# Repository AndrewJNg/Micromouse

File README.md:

# Micromouse
Micromouse alagorithm for solving a maze with known size

## Current robot: 
1. Homemade micromouse (Arduino Micro) 
2. ESP32 micromouse

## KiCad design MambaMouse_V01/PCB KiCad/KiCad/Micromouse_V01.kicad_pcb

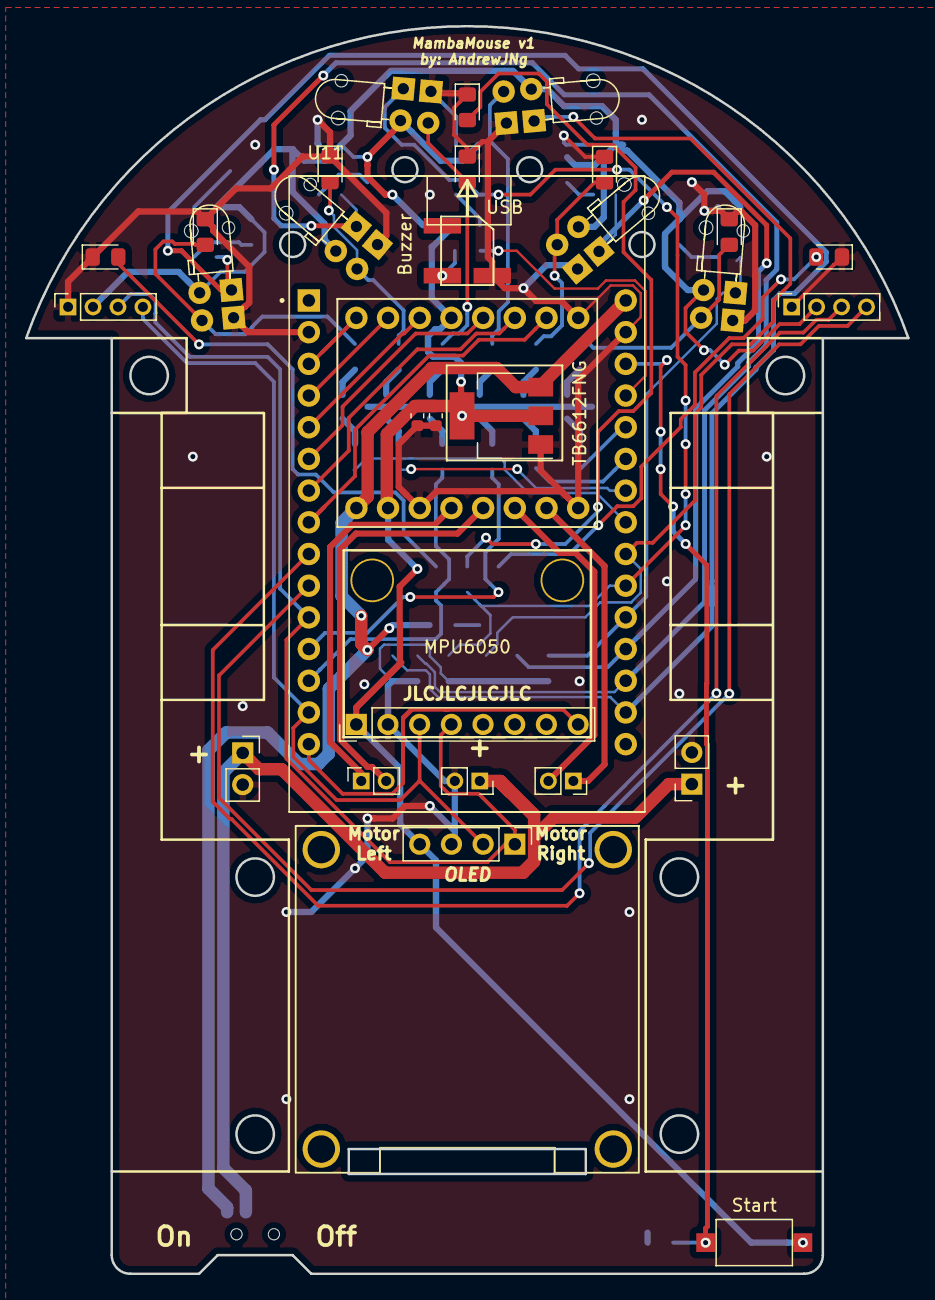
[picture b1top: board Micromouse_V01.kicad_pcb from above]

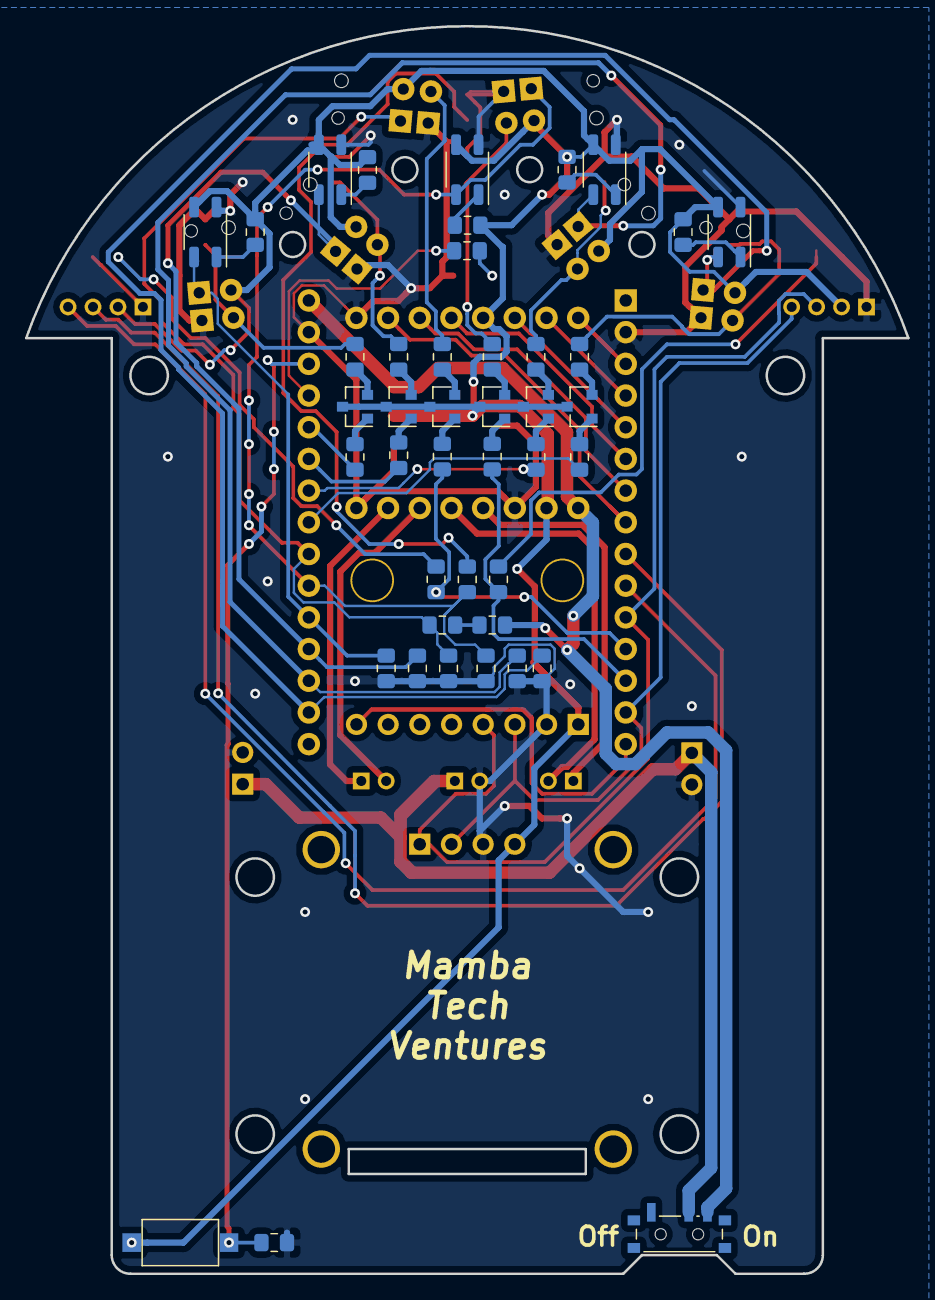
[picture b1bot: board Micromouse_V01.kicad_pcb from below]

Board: 2 copper layers, 70.7 x 100.0 mm, 73 parts (43 on the bottom side), 61 nets.

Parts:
BZ1: Buzzer; 4.2mm_5.5mm buzzer
C1, C2: 100nF; C_0603_1608Metric
D1, D2, D3, D4, D5, D6, D7, D8: LED; LED_0805_2012Metric_Pad1.15x1.40mm_HandSolder
J1, J7: Conn_01x02_Female; PinSocket_1x02_P2.54mm_Vertical
J2, J4, J8: Conn_01x02_Female; PinSocket_1x02_P2.00mm_Vertical
J3: OLED; OLED 128x32
J5: AS5600 Left; PinSocket_1x04_P2.00mm_Vertical
J6: AS5600 Right; PinSocket_1x04_P2.00mm_Vertical
Q1, Q2, Q3, Q4, Q5, Q6: Q_NPN_BEC; SOT-23
R1, R3, R5, R7, R9, R11, R15, R16, R17, R19, R26, R27, R28, R29, R30: 100; R_0805_2012Metric_Pad1.15x1.40mm_HandSolder
R2, R4, R6, R8, R10, R12, R13, R14, R18: 10K; R_0805_2012Metric_Pad1.15x1.40mm_HandSolder
R20, R21, R22, R23, R24, R25: 1k; R_0805_2012Metric_Pad1.15x1.40mm_HandSolder
S1, S2, S3, S4, S5, S6: 3mm_IR
S7, S8, S9, S10, S11: QRE1113; OnSemi_CASE100CY
SW1: SW_DPDT_x2; SW_SPDT_PCM12
SW2, SW3: Start; SW_SPST_CK_RS282G05A3
U1: AMS1117-3.3; SOT-223-3_TabPin2
U11: ESP32-WROOM; MODULE_ESP32_DEVKIT_V1
U12: TB6612FNG
U13: MPU-6050; MPU6050 module

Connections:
1: R15.1, R25.2, U11.35
2: U11.24, U12.22
3: R17.1, R20.2, U11.34
4: U11.26, U12.21
5: U11.29, U12.15
12: R19.1, U11.14
13: R18.2, SW2.2, SW3.2, U11.16
14: R24.2, U11.13
15: U11.23, U12.23
16: U11.27, U12.17
17: U11.28, U12.16
18_SDA2: J6.3, U11.30
19_SCL2: J6.4, U11.31
21_SDA1: J3.4, J5.3, U11.33, U13.24
22_SCL1: J3.3, J5.4, U11.36, U13.23
23: U11.37, U13.12
25: R21.2, U11.10
26: R22.2, U11.11
27: R23.2, U11.12
32: R10.1, R16.1, S5.3, S9.4, U11.8
33: R12.1, R14.2, S6.3, U11.9
34: R6.1, S3.3, S10.4, U11.6
35: R8.1, S4.3, S11.4, U11.7
36: R2.1, S1.3, S7.4, U11.4
39: R4.1, S2.3, S8.4, U11.5
+3V3: C1.1, C2.1, J3.1, J5.2, J6.2, Q1.3, Q2.3, Q3.3, Q4.3, Q5.3, Q6.3, R26.1, R27.1, R28.1, R29.1, R30.1, S1.4, S2.4, S3.4, S4.4, S5.4, S6.4, S7.3, S8.3, S9.3, S10.3, S11.3, SW2.1, SW3.1, U1.2, U12.19, U12.20, U13.13
+BATT: J1.1, J7.1, J8.1, SW1.2
GND: BZ1.2, C1.2, C2.2, D1.1, D2.1, D3.1, D4.1, D5.1, D6.1, D7.1, D8.1, J1.2, J3.2, J5.1, J6.1, J7.2, J8.2, R2.2, R4.2, R6.2, R8.2, R10.2, R12.2, R18.1, S1.1, S2.1, S3.1, S4.1, S5.1, S6.1, S7.2, S8.2, S9.2, S10.2, S11.2, U1.1, U11.15, U12.4, U12.9, U12.18, U13.18
unnamed: BZ1.1, R19.2
unnamed: D1.2, R15.2
unnamed: D2.2, R16.2
unnamed: D3.2, R17.2
unnamed: D4.2, R1.2, S1.2
unnamed: D5.2, R3.2, S2.2
unnamed: D6.2, R9.2, S5.2
unnamed: D7.2, R5.2, S3.2
unnamed: D8.2, R7.2, S4.2
unnamed: J2.1, U12.1
unnamed: J2.2, U12.5
unnamed: J4.1, U12.11
unnamed: J4.2, U12.7
unnamed: Q1.1, R21.1
unnamed: Q1.2, R1.1
unnamed: Q2.1, R22.1
unnamed: Q2.2, R3.1
unnamed: Q3.1, R23.1
unnamed: Q3.2, R5.1
unnamed: Q4.1, R24.1
unnamed: Q4.2, R7.1
unnamed: Q5.1, R25.1
unnamed: Q5.2, R9.1
unnamed: Q6.1, R20.1
unnamed: Q6.2, R11.1
unnamed: R11.2, S6.2
unnamed: R13.2, R14.1
unnamed: R26.2, S9.1
unnamed: R27.2, S7.1
unnamed: R28.2, S8.1
unnamed: R29.2, S10.1
unnamed: R30.2, S11.1
VCC: R13.1, SW1.3, U1.3, U11.32, U12.14

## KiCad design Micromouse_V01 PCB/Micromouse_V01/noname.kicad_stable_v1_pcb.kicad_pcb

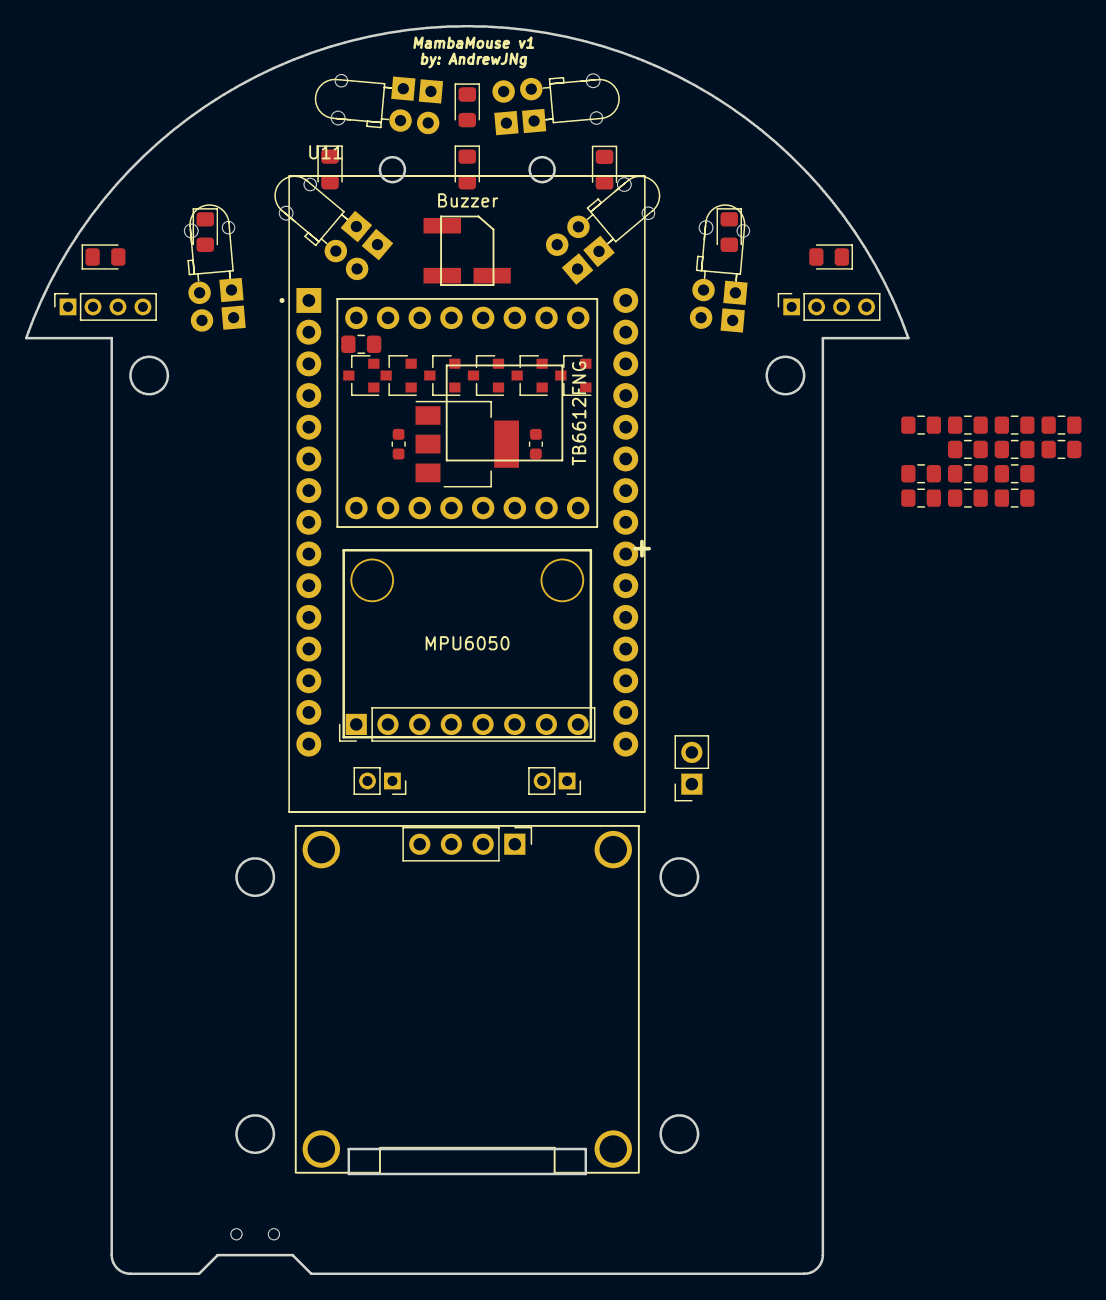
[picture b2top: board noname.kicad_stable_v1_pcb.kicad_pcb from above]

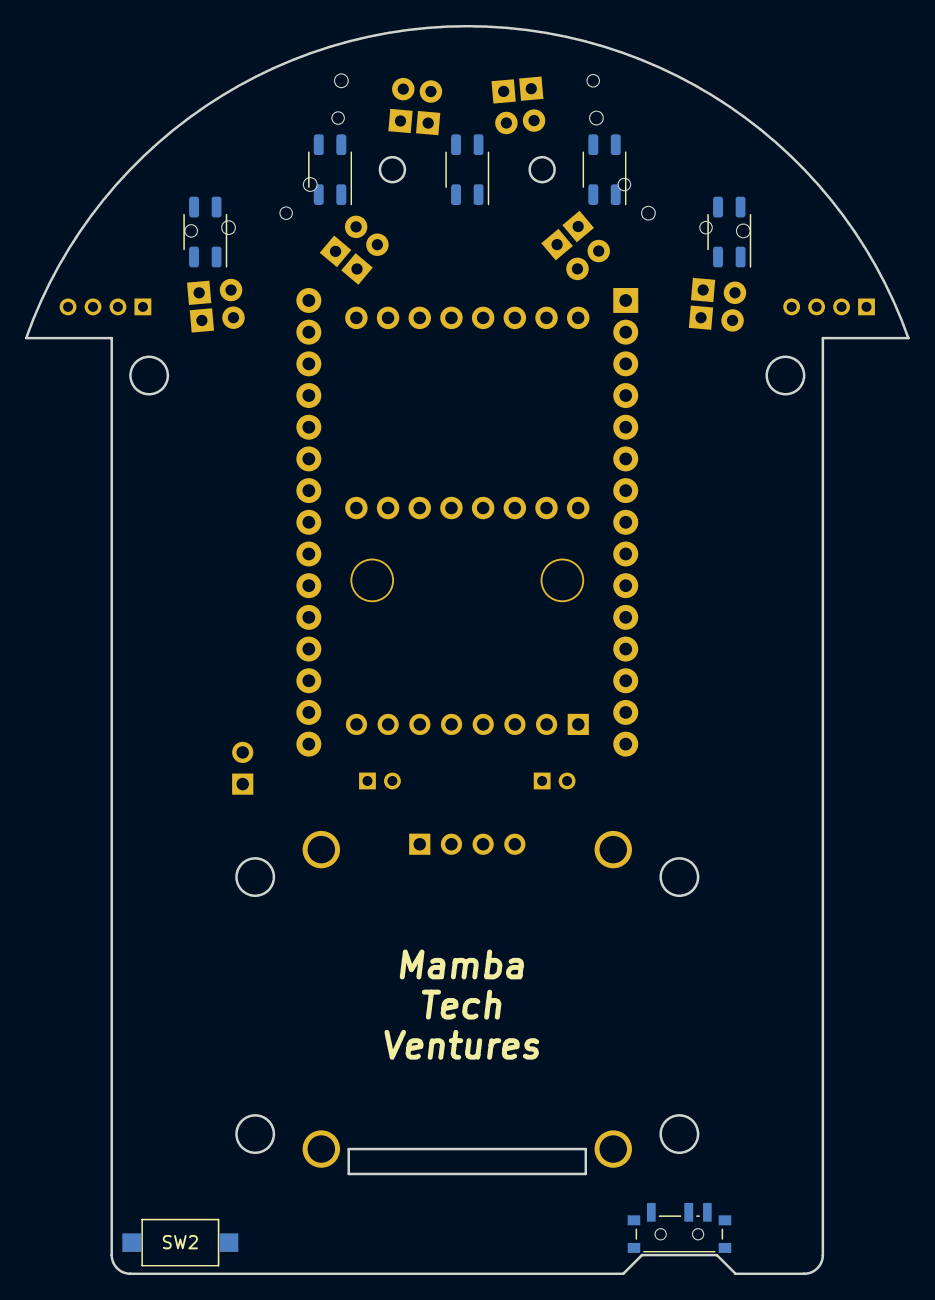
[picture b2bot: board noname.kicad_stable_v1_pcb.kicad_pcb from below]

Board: 2 copper layers, 70.7 x 100.0 mm, 54 parts (7 on the bottom side), 24 nets, no tracks yet.

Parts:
BZ1: Buzzer; 4.2mm_5.5mm buzzer
C1, C2: 100nF; C_0603_1608Metric
D1, D2, D3, D4, D5, D6, D7, D8: LED; LED_0805_2012Metric_Pad1.15x1.40mm_HandSolder
J1: Conn_01x02_Female; PinSocket_1x02_P2.54mm_Vertical
J2, J4: Conn_01x02_Female; PinSocket_1x02_P2.00mm_Vertical
J3: OLED; OLED 128x32
J5: AS5600 Right; PinSocket_1x04_P2.00mm_Vertical
J6: AS5600 Left; PinSocket_1x04_P2.00mm_Vertical
Q1, Q2, Q3, Q4, Q5, Q6: Q_NPN_BEC; SOT-23
R1, R3, R5, R7, R9, R11, R13: 10K; R_0805_2012Metric_Pad1.15x1.40mm_HandSolder
R2, R4, R6, R8, R10, R12, R14: 220; R_0805_2012Metric_Pad1.15x1.40mm_HandSolder
S1, S2, S3, S4, S5, S6: 3mm_IR
SW1: SW_DPDT_x2; SW_SPDT_PCM12
SW2: Start; SW_SPST_CK_RS282G05A3
U1: AMS1117-3.3; SOT-223-3_TabPin2
U2, U3, U8, U9, U10: QRE1113GR; OnSemi_CASE100CY
U11: ESP32-WROOM; MODULE_ESP32_DEVKIT_V1
U12: TB6612FNG
U13: MPU-6050; MPU6050 module

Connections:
+3V3: C1.1, C2.1, J3.1, Q1.3, Q2.3, Q3.3, Q4.3, Q5.3, Q6.3, S1.4, S2.4, S3.4, S4.4, S5.4, S6.4, U1.2
+BATT: J1.1, SW1.2
A0: R3.1, S1.3
A1: R5.1, S2.3
A2: R7.1, S3.3
A3: R9.1, S4.3
A6: R11.1, S5.3
A7: R13.1, S6.3
D8: R1.2, SW2.2
GND: BZ1.2, C1.2, C2.2, J1.2, J3.2, R1.1, R3.2, R5.2, R7.2, R9.2, R11.2, R13.2, S1.1, S2.1, S3.1, S4.1, S5.1, S6.1, U1.1
unnamed: BZ1.1, R14.2
unnamed: Q1.2, R2.1
unnamed: Q2.2, R4.1
unnamed: Q3.2, R6.1
unnamed: Q4.2, R8.1
unnamed: Q5.2, R10.1
unnamed: Q6.2, R12.1
unnamed: R2.2, S1.2
unnamed: R4.2, S2.2
unnamed: R6.2, S3.2
unnamed: R8.2, S4.2
unnamed: R10.2, S5.2
unnamed: R12.2, S6.2
VCC: SW1.1, U1.3

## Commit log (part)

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2022-01-25 Stable release (Working floodfill algorithem )
2022-01-25 made changes to allow speed run if needed
2022-01-25 made major changes to the floodfill algorithm
2022-01-25 made passing through known cells faster, along with virtual checking (if fastest path is all on known cells)
2022-02-17 Develop the ESP32 arduino code to solve real world maze
2022-02-17 counter mistake in adding arduino ESP32 micromouse code
2022-02-22 Stable release
2022-07-04 Made first version with fundamental components list, with raw sensor inputs
2022-07-04 improved on as5600 encoder sensing, made it so encoder have a menu counter and a high speed motor counter
2022-07-05 cleaned up the main file, calculation for speed using encoders, aligning to front wall using infrared values and simple proportional code, added cell_mevement which allows for maze movements and turn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
2022-07-06 added maze centering (keep robot in the middle of walls), added menu system using ps3 controller to change mode, and OLED menu from mamba Samurai robot, added ps3 battery monitoring to show on OLED
2022-07-07 added PID library and ps3 support for easy kp ki kd value change along with displaying the values on the OLED display. Button class was made to allow easy changes using inputs from different IR senso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
2022-07-08 made a semi successful velocity control system (encoder seems to be jumping every now and again, PID could be improved as one motor is faster thatn the other still)
2022-07-08 moved the speed monitoring system to a function in speed_profile, removed the IR sensor as they are blocking the code, which improves the calculation for the wheel
2022-07-09 found the main bug for encoder skips (added equal sign to encoder reading statement), commented out encoder motor as the speed improvement from the previous days for as5600 configuration has eliminat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
2022-07-09 made turn function to accept a parameter for degree to turn instead of 1,2,3,4
2022-07-09 combined menu encoder update and enc motor update, as it is not needed anymore as the i2c speed of as5600 is able to support the speed needed
2022-07-09 improved turn() fucntion using PID tuning
2022-07-13 made lots of changes, main addition is to use pointers as map variable, made a c++ file for pointers in another file, refined movement functions to be able to swap between alignment tools based on wa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
2022-07-13 furnished the OLED display with floodfill numerics, X and arrows for target and robot position and direction, this save would be used as a backup for merging the code to the main code
2022-07-14 made minor changes to cell movements in hopes to make maze sensing more reliable, however wasn't quite successful
2022-12-16 added in V1 PCB design files
2023-01-18 added mamba mouse line tracer, made another PID control system using arduino PID library
2023-01-28 added bluetooth to phone function to instruct directions
2023-06-03 made minor changes to the code for different modes, added a new combined sensor mount for ir sensors
2023-06-13 added memory storage, refined linear infrared sensing with normalised values, used simpler lowPass filter function online, added encoder menu system to swap between modes and use right infrareds for 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
2024-09-08 backup after long time, to update kicad
2024-10-26 Clean up repo files and versions
2024-10-26 issue with encoder, next step is to make it a class
2024-10-26 used AS5600 library instead of self written one
2024-10-26 moved motor pwm to 12 bit, 4096 steps for better motor control
2024-10-28 made a subsystem function, with encoder and motor built together as a class,
2024-10-28 removed commented out code, and add lowpass filter to encoder wheel
2024-10-28 generated trapezoidal velocity profile, combined method works quite well, however there is a motor loading issue, feedforward a term not tuned, and PID values are not tuned, however gave 10cm precisi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
